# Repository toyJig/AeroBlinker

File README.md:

# AeroBlinker
Custom PCB w/ KiCAD that reads Receiver Signals to control light flash patterns - Aeronautics Team.

Read [JOURNAL.md](https://github.com/toyJig/AeroBlinker/blob/main/JOURNAL.md) for the logged process!
JLCPCB BOM is located [here](https://github.com/toyJig/AeroBlinker/blob/main/jlcpcb/production_files/BOM-AeroBlinker.csv)!

Overall BOM:

| Thing | Unit Price | Amount | 
| :--- | :--- | :--- |
| A STM32F042F6P6 MCU PCB assembled at JLC | $14.96 | 5 | 
| 2v2 700mA LED | Club has | 3 |
| 700maH 1S LiPo | Club has | 1 |

| Features: |
| -------- |
| A small STM32F042F6P6 MCU that decodes PWM frequencies to control a MOSFET |
| USB-C flashing and a LDO regulator for the USB-C VBUS (the STM can't handle 5V) |
| An on-board 3.3v Buck Convertor to step down efficiently from 1S or 2S Voltages |
| Connectors to connect up to 3 LEDs with (Can wire more in series if needed) |

View the PCB Here!:

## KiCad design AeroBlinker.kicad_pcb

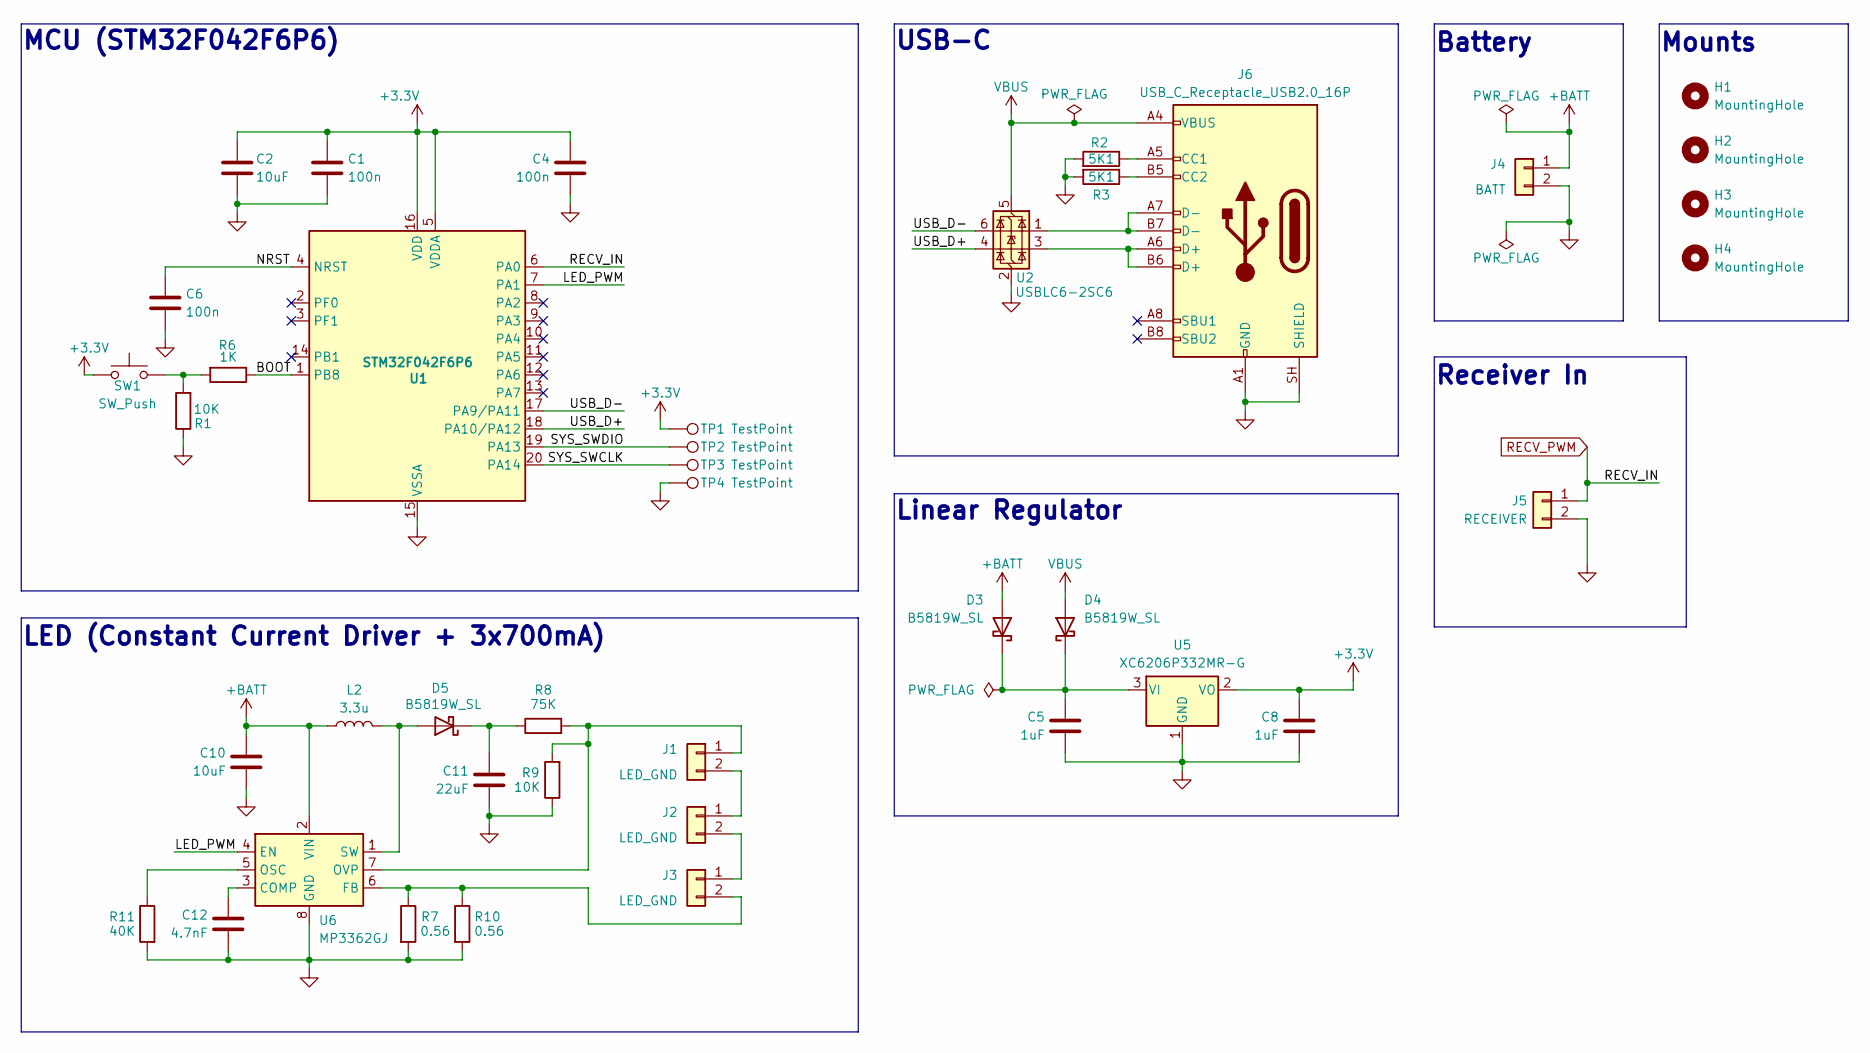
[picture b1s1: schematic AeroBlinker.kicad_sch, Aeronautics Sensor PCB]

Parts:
C1, C4, C6: 100n; C_0402_1005Metric; LCSC C1525
C2: 10uF; C_0603_1608Metric; LCSC C19702
C5, C8: 1uF; C_0402_1005Metric; LCSC C1525
C10: 10uF; C_0603_1608Metric; LCSC C59461
C11: 22uF; C_0805_2012Metric; LCSC C59461
C12: 4.7nF; C_0402_1005Metric; LCSC C59461
D3, D4, D5: B5819W_SL; D_SOD-123; LCSC C8598
H1, H2, H3, H4: MountingHole; MountingHole_2.1mm
J1, J2, J3: LED_GND; JST_XH_B2B-XH-A_1x02_P2.50mm_Vertical; LCSC C158012
J4: BATT; JST_VH_B2P-VH_1x02_P3.96mm_Vertical; LCSC C160315
J5: RECEIVER; JST_XH_B2B-XH-A_1x02_P2.50mm_Vertical; LCSC C158012
J6: USB_C_Receptacle_USB2.0_16P; USB_C_Receptacle_GCT_USB4105-xx-A_16P_TopMnt_Horizontal; LCSC C3025063
L2: 3.3u; IND-SMD_L4.0-W4.0_0.47UH04209.5A
R1: 10K; R_0402_1005Metric; LCSC C25744
R2, R3: 5K1; R_0402_1005Metric; LCSC C25905
R6: 1K; R_0402_1005Metric; LCSC C11702
R7, R10: 0.56; R_0402_1005Metric; LCSC C11702
R8: 75K; R_0402_1005Metric; LCSC C11702
R9: 10K; R_0402_1005Metric; LCSC C11702
R11: 40K; R_0402_1005Metric; LCSC C11702
SW1: SW_Push; SW-SMD_L3.9-W3.0-P4.45; LCSC C269272
TP1, TP2, TP3, TP4: TestPoint; TestPoint_Pad_1.5x1.5mm
U1: STM32F042F6P6; TSSOP-20_4.4x6.5mm_P0.65mm; LCSC C81000
U2: USBLC6-2SC6; SOT-23-6; LCSC C2827654
U5: XC6206P332MR-G; SOT-23-3; LCSC C5446
U6: MP3362GJ; TSOT-23-8

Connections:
+3.3V: C1.1, C2.1, C4.1, C8.1, SW1.1, TP1.1 (1_1), U1.5 (VDDA), U1.16 (VDD), U5.2 (VO)
+BATT: C10.1, D3.2 (A), J4.1, L2.1, U6.2 (VIN)
/BOOT: R6.1, U1.1 (PB8)
/LED_PWM: U1.7 (PA1), U6.4 (EN)
/NRST: C6.1, U1.4 (NRST)
/SYS_SWCLK: TP3.1 (1_1), U1.20 (PA14)
/SYS_SWDIO: TP2.1 (1_1), U1.19 (PA13)
/USB_D+: U1.18 (PA10/PA12), U2.4 (I/O2)
/USB_D-: U1.17 (PA9/PA11), U2.6 (I/O1)
GND: C1.2, C2.2, C4.2, C5.2, C6.2, C8.2, C10.2, C11.2, C12.2, J4.2, J5.2, J6.A1 (GND), J6.A12 (GND), J6.B1 (GND), J6.B12 (GND), J6.SH (SHIELD), R1.1, R2.2, R3.2, R7.2, R9.1, R10.2, R11.2, TP4.1 (1_1), U1.15 (VSSA), U2.2 (GND), U5.1 (GND), U6.8 (GND)
unnamed: C5.1, D3.1 (K), D4.1 (K), U5.3 (VI)
unnamed: D5.2 (A), L2.2, U6.1 (SW)
unnamed: C11.1, D5.1 (K), R8.1
unnamed: J1.1, R8.2, R9.2, U6.7 (OVP)
unnamed: J1.2, J2.1
unnamed: J2.2, J3.1
unnamed: J3.2, R7.1, R10.1, U6.6 (FB)
unnamed: J6.A5 (CC1), R2.1
unnamed: J6.B5 (CC2), R3.1
unnamed: J6.A6 (D+), J6.B6 (D+), U2.3 (I/O2)
unnamed: J6.A7 (D-), J6.B7 (D-), U2.1 (I/O1)
unnamed: R1.2, R6.2, SW1.2
unnamed: C12.1, U6.3 (COMP)
unnamed: R11.1, U6.5 (OSC)
RECV_PWM: J5.1, U1.6 (PA0)
VBUS: D4.2 (A), J6.A4 (VBUS), J6.A9 (VBUS), J6.B4 (VBUS), J6.B9 (VBUS), U2.5 (VBUS)

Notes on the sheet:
USB-C
LED (Constant Current Driver + 3x700mA)
Linear Regulator
Battery
Mounts
MCU (STM32F042F6P6)
Receiver In

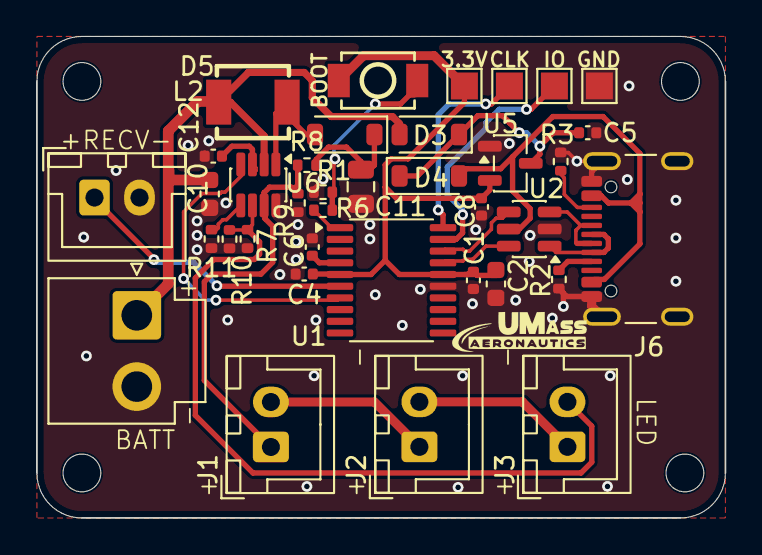
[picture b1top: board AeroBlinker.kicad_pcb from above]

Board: 2 copper layers, 38.2 x 26.8 mm, 41 parts (0 on the bottom side), 26 nets.

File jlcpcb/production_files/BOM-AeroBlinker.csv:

Comment,Designator,Footprint,LCSC,Quantity
0.56,"R10,R7",R_0402_1005Metric,C423099,2
100n,"C1,C4,C6",C_0402_1005Metric,C1525,3
10K,"R1,R9",R_0402_1005Metric,C25744,2
10uF,"C10,C2",C_0603_1608Metric,C19702,2
1K,R6,R_0402_1005Metric,C11702,1
1uF,"C5,C8",C_0402_1005Metric,C52923,2
22u,C11,C_0805_2012Metric,C45783,1
3.3u,L2,IND-SMD_L4.0-W4.0_0.47UH04209.5A,C438931,1
4.7nF,C12,C_0402_1005Metric,C1538,1
40K,R11,R_0402_1005Metric,C49654409,1
5K1,"R2,R3",R_0402_1005Metric,C25905,2
75K,R8,R_0402_1005Metric,C25798,1
B5819W_SL,"D3,D4,D5",D_SOD-123,C8598,3
BATT,J4,JST_VH_B2P-VH_1x02_P3.96mm_Vertical,C160315,1
LED_GND,"J1,J2,J3",JST_XH_B2B-XH-A_1x02_P2.50mm_Vertical,C158012,3
MP3362GJ,U6,TSOT-23-8,C3194309,1
RECEIVER,J5,JST_XH_B2B-XH-A_1x02_P2.50mm_Vertical,C158012,1
STM32F042F6P6,U1,TSSOP-20_4.4x6.5mm_P0.65mm,C81000,1
SW_Push,SW1,SW-SMD_L3.9-W3.0-P4.45,C269272,1
USBLC6-2SC6,U2,SOT-23-6,C2827654,1
USB_C_Receptacle_USB2.0_16P,J6,USB_C_Receptacle_GCT_USB4105-xx-A_16P_TopMnt_Horizontal,C3025063,1
XC6206P332MR-G,U5,SOT-23-3,C5446,1
